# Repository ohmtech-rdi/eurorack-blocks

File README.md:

# eurorack-blocks

[<!--lint ignore no-dead-urls-->](https://github.com/ohmtech-rdi/eurorack-blocks/actions?workflow=Ubuntu%2020.04)
[<!--lint ignore no-dead-urls-->](https://github.com/ohmtech-rdi/eurorack-blocks/actions?workflow=macOS%2011)
[<!--lint ignore no-dead-urls-->](https://github.com/ohmtech-rdi/eurorack-blocks/actions?workflow=Windows%202019)

The `eurorack-blocks` project allows to develop your own custom Eurorack module for either
prototyping or fun in the comfort of your day-to-day IDE with the C++ or Faust language,
or using the Cycling '74 Max environment,
testing and debugging in a [virtual Eurorack environment](https://vcvrack.com),
and when ready, to auto-magically generate all the needed files to manufacture
the eurorack module for you to use in a real Eurorack modular system.

`eurorack-blocks` is using [`Daisy Patch Submodule`](https://www.electro-smith.com/daisy/patch-sm),
a DSP platform for Eurorack synthesizer modules. It features a lightning fast STM32 processor,
high fidelity stereo audio codec, and enough RAM for 10 minute long buffers
— all with standard signal levels and conditioning for the Eurorack ecosystem.

The [documentation as well as the Getting Started guide can be found on **Read the Docs**](https://eurorack-blocks.readthedocs.io/en/latest/).

The full project's manifest can be read [here](manifest.md).

```cpp
// Bypass.h

#include "artifacts/BypassUi.h"

struct Bypass {
   BypassUi ui;

   void process () {
      ui.audio_out = ui.audio_in;
   }
};
```

```erb
// Bypass.erbui

module Bypass {
   width 8hp
   material aluminum black
   header { label "BYPASS" }

   control audio_in AudioIn {
      position 4hp, 40mm
      label "IN"
   }

   control audio_out AudioOut {
      position 4hp, 80mm
      label "OUT"
   }
}
```

```console
raf:bypass$ erbb configure 👈 Generate IDE projects
raf:bypass$ ls -l artifacts/
drwxr-xr-x  7 raf  staff  224 Feb  9 18:31 actions
drwxr-xr-x  3 raf  staff   96 Feb  9 18:31 daisy 👈 Daisy firmware build files
drwxr-xr-x  3 raf  staff   96 Feb  9 18:31 simulator 👈 Simulator build files
-rw-r--r--  1 raf  staff  109 Feb  9 18:31 Bypass.code-workspace 👈 Visual Studio Code Workspace
drwxr-xr-x  3 raf  staff   96 Feb  9 18:31 project_vcvrack.xcodeproj 👈 Simulator Xcode Project
raf:bypass$ erbb build simulator 👈 Build the simulator for VCV Rack
...
** BUILD SUCCEEDED **
raf:bypass$ open /Applications/Rack.app 👈 Test in VCV Rack and iterate
raf:bypass$ erbb build hardware 👈 Build the hardware files for manufacturing
raf:bypass$ ls -l artifacts/hardware/
-rw-r--r--   1 raf  staff     387 Feb  9 18:31 Bypass.bom.csv 👈 Bill of materials
-rw-r--r--   1 raf  staff   15696 Feb  9 18:31 Bypass.dxf 👈 Aluminum panel milling/drilling
-rw-r--r--   1 raf  staff   32731 Feb  9 18:31 Bypass.gerber.zip 👈 PCB Gerber files
-rw-r--r--   1 raf  staff  116908 Feb  9 18:31 Bypass.kicad_pcb
-rw-r--r--   1 raf  staff    4754 Feb  9 18:31 Bypass.pdf 👈 Aluminum panel UV printing
drwxr-xr-x  12 raf  staff     384 Feb  9 18:31 gerber
raf:bypass$ erbb build 👈 Build the firmware
ninja: Entering directory `.../eurorack-blocks/samples/bypass/artifacts/daisy/out/Release'
[191/191] LINK Bypass
OBJCOPY Bypass
raf:bypass$ erbb install 👈 Upload the firmware
Enter the system bootloader by holding the BOOT button down,
and then pressing, and releasing the RESET button.
Press Enter to continue...
...
raf:bypass$
```

## Sample Projects

<p align="center">

</p>

Before reading sample code, make sure to grasp the concepts in the [documentation](https://eurorack-blocks.readthedocs.io/en/latest/).
Sample projects are a good place to continue learning:

- [`bypass`](./samples/bypass/) is the example used above,
- [`drop`](./samples/drop/) shows the usage of almost every blocks,
- [`reverb`](./samples/reverb/) illustrates how to utilize all the platform memory,
- [`kick`](./samples/kick/) illustrates how to use factory samples and make big programs,
- [`faust`](./samples/faust/) describes how to use the Faust functional programming language,
- [`custom`](./samples/custom/) illustrates how to use custom silkscreens, boards and manufacturers,
- [`frohmager`](./samples/frohmager/) is the recreation in hardware form factor of the legendary Ohm Force multi-band resonant filter (closed-source).

## Cycling '74 Max Patches

First make sure to read the [Max integration documentation](https://eurorack-blocks.readthedocs.io/en/latest/max/setup.html).
Sample projects are a good place to continue learning:

- [`reverb`](./max/reverb/) uses Gigaverb.
- [`drop`](./max/drop/) shows the usage of almost every blocks.

## Setting up

Setting up the development environment is described in the
[documentation](https://eurorack-blocks.readthedocs.io/en/latest/setup/select.html).
Integrations might have also their own Set up documentation, so make sure to read this as well.

## Structure

```
eurorack-blocks/
   blocks/
   boards/
   build-system/
   include/
   max/
   src/
   submodules/
```

- [`blocks`](./blocks/) contains all the atomic blocks hardware for design validation and software tests,
- [`boards`](./blocks/) contains all the boards hardware to design with,
- [`build-system`](./build-system/) contains the build system used to build and deploy
   the tests and samples,
- [`include`](./include/) contains the software implementation of the blocks,
- [`max`](./max/) contains the Cycling '74 Max integration,
- [`src`](./src/) contains the software implementation of the blocks,
- [`submodules`](./submodules/) contains the software dependencies as submodules.

## License

All files in this repository, excluding `submodules/`, are provided with the CC BY-SA 4.0 license
for the hardware part, and MIT license for the software part, **except**:

- The [Cycling '74 Max Gen DSP Source Code](./include/gen_dsp),
- The [D-DIN Font](./include/erb/vcvrack/design/d-din),
   under [SIL Open Font License](./include/erb/vcvrack/design/d-din/SIL%20Open%20Font%20License.txt),
- The [Indie Flower Font](./include/erb/vcvrack/design/indie-flower),
   under [SIL Open Font License](./include/erb/vcvrack/design/indie-flower/OFL.txt),
- The [Rogan... files](./include/erb/vcvrack/resource),
   as derivative work of some VCV Rack files under the [VCV Rack GPLv3 License](https://github.com/VCVRack/Rack/blob/v2/LICENSE-GPLv3.txt),
- The [Arpeggio project](https://github.com/textX/Arpeggio), under the [MIT License](https://textx.github.io/Arpeggio/stable/about/license/),
- The [Custom panel artwork](https://svgsilh.com/image/1532531.html), under the [Creative Commons CC0 License](https://creativecommons.org/publicdomain/zero/1.0/).
- The Ohm Force Frohmager, under its proprietary license.

Some files that get installed in `build-system/toolchain` during `erbb setup` are not part of this repository, but redistributed during the installation phase,
with the following licenses:
   - [dfu-util](https://dfu-util.sourceforge.net) under the [GPL version 2](https://sourceforge.net/p/dfu-util/dfu-util/ci/master/tree/COPYING),
   - [Cairo](https://www.cairographics.org) under the [GNU Lesser General Public License (LGPL) version 2.1 or the Mozilla Public License (MPL) version 1.1](https://gitlab.freedesktop.org/cairo/cairo/-/blob/master/COPYING),
   - [libcapstone](https://github.com/libcapstone/libcapstone) under the [3-Clause BSD License](https://github.com/libcapstone/libcapstone/blob/main/LICENSE.TXT),
   - [Fontconfig](https://www.freedesktop.org/wiki/Software/fontconfig/) under the [MIT License](https://gitlab.freedesktop.org/fontconfig/fontconfig/-/blob/main/COPYING),
   - [Freetype](https://freetype.org) under the [Freetype license or  GNU General Public License (GPL), version 2](https://freetype.org/license.html),
   - [libftdi](https://www.intra2net.com/en/developer/libftdi/), which [library is licensed under LGPL 2.1 (not any later)](http://developer.intra2net.com/git/?p=libftdi;a=blob;f=COPYING.LIB;h=5bc8fb2c8f757e34a0d8f4644f589d57609e213f;hb=HEAD), and [EEPROM programmer is licensed under GPL 2 (not any later)](http://developer.intra2net.com/git/?p=libftdi;a=blob;f=COPYING.GPL;h=d511905c1647a1e311e8b20d5930a37a9c2531cd;hb=HEAD),
   - [libhidapi](https://github.com/libusb/hidapi), under the [GNU General Public License, version 3.0](https://github.com/libusb/hidapi/blob/master/LICENSE-gpl3.txt), [BSD-Style License](https://github.com/libusb/hidapi/blob/master/LICENSE-bsd.txt) or [more liberal original HIDAPI license](https://github.com/libusb/hidapi/blob/master/LICENSE-orig.txt),
   - [libpixman](https://github.com/libpixman/pixman) under the [MIT license](https://github.com/libpixman/pixman/blob/master/COPYING),
   - [libpng](http://www.libpng.org/pub/png/libpng.html) under the [PNG Reference Library License version 2](http://www.libpng.org/pub/png/src/libpng-LICENSE.txt),
   - [libusb](https://github.com/libusb/libusb) under the [GNU Lesser General Public License v2.1](https://github.com/libusb/libusb/blob/master/COPYING),
   - [Xorg libraries](https://gitlab.freedesktop.org/xorg/lib) under the [MIT license](https://gitlab.freedesktop.org/xorg/lib/libx11/-/blob/master/COPYING),
   - [openocd](https://openocd.org) under the [GPL-2.0-or-later](https://sourceforge.net/p/openocd/code/ci/master/tree/COPYING)
   - [GNU Arm Embedded Toolchain](https://developer.arm.com/downloads/-/gnu-rm) under various licenses, navigate to `build-system/toolchain/gcc-arm-none-eabi-10.3-2021.10/share/doc/gcc-arm-none-eabi/license.txt` for a complete list,
   - [KiCad](https://www.kicad.org) under its [license](https://gitlab.com/kicad/code/kicad/-/blob/master/LICENSE).

Redistribution of your firmware for commecial purposes only have a subset of those licences:
- Modules which firmware was code generated by Gen from a patcher is dual licensed under the [Cycling '74 License for Max-Generated Code for Export](https://support.cycling74.com/hc/en-us/articles/10730031661587) or [GPLv3](https://www.gnu.org/licenses/gpl-3.0.en.html). 
- Eurorack-blocks framework is under the MIT license,
- [libDaisy](https://github.com/electro-smith/libDaisy) is under the [MIT license](https://github.com/electro-smith/libDaisy/blob/master/LICENSE),
- [GNU Arm Embedded Toolchain libraries](https://developer.arm.com/downloads/-/gnu-rm) under various licenses, navigate to `build-system/toolchain/gcc-arm-none-eabi-10.3-2021.10/share/doc/gcc-arm-none-eabi/license.txt` for a complete list.

Redistribution of your panel, if using the font in this repository:
- The [D-DIN Font](./include/erb/vcvrack/design/d-din), under [SIL Open Font License](./include/erb/vcvrack/design/d-din/SIL%20Open%20Font%20License.txt),

To fullfil attribution, users will generally put the ERB logo and the URL to this project, on their PCB like in [this example](https://blogger.googleusercontent.com/img/b/R29vZ2xl/AVvXsEjbp3qvEp6JkepX6Xh4_h2b57rY708SmwVZjv8ANe1bIvhrfsvV8bGgZkJezpeA5sWZmZln5WsoP8231fTwboIVxd3dbACfYKJyjOHhfvMlSTO7WLXSDi_nQDXI3Ygvw2XLOCR4dY4M1gGWNpXnzImI5TEGjqsB7BOLt36qAzrYm9yt0QguTqL6EOvM/s4032/TopographeBack.jpeg) (courtesy of [Oms in serial](https://omsinserial.blogspot.com))

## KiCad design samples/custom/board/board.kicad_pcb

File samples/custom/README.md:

# Custom

`Custom` is a sample to illustrate the use of custom images, boards and manufacturers.

[Artwork](https://svgsilh.com/image/1532531.html) from [Leunert](https://pixabay.com/users/leunert-2332372/) released under [Public Domain — Creative Commons CC0](https://creativecommons.org/publicdomain/zero/1.0/).

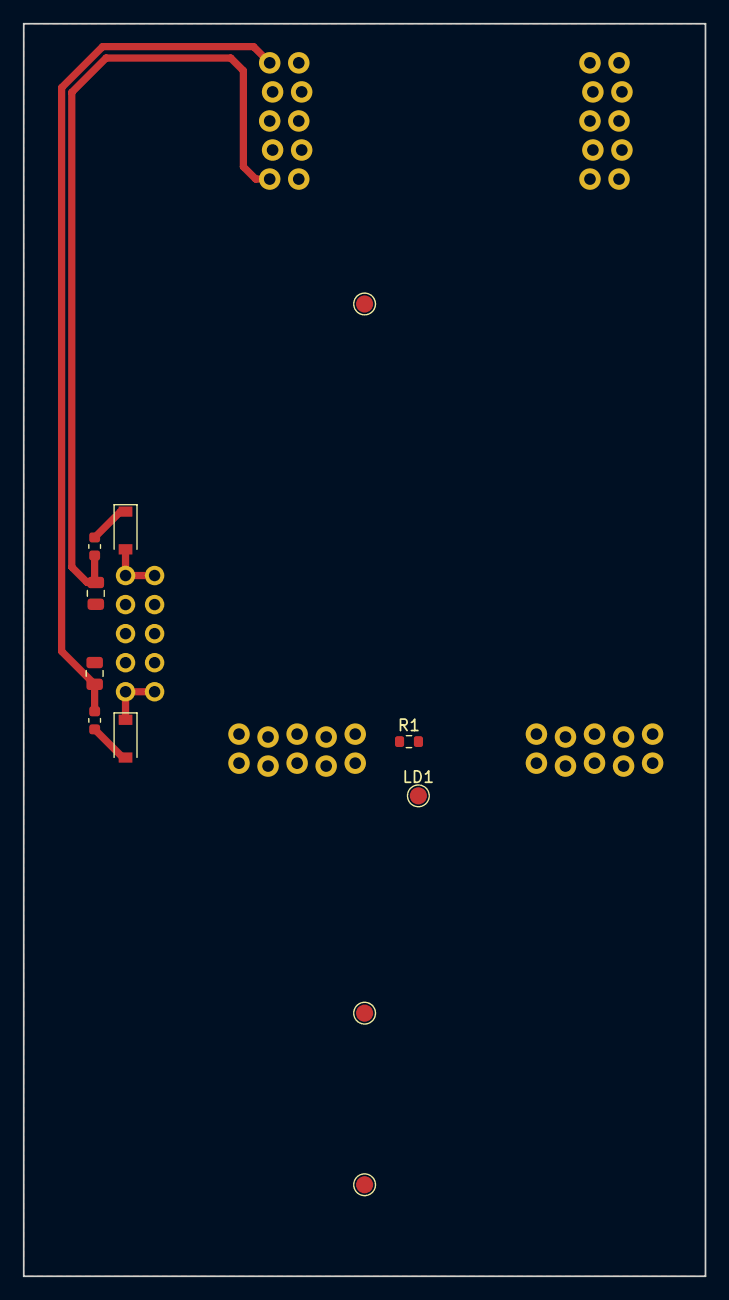
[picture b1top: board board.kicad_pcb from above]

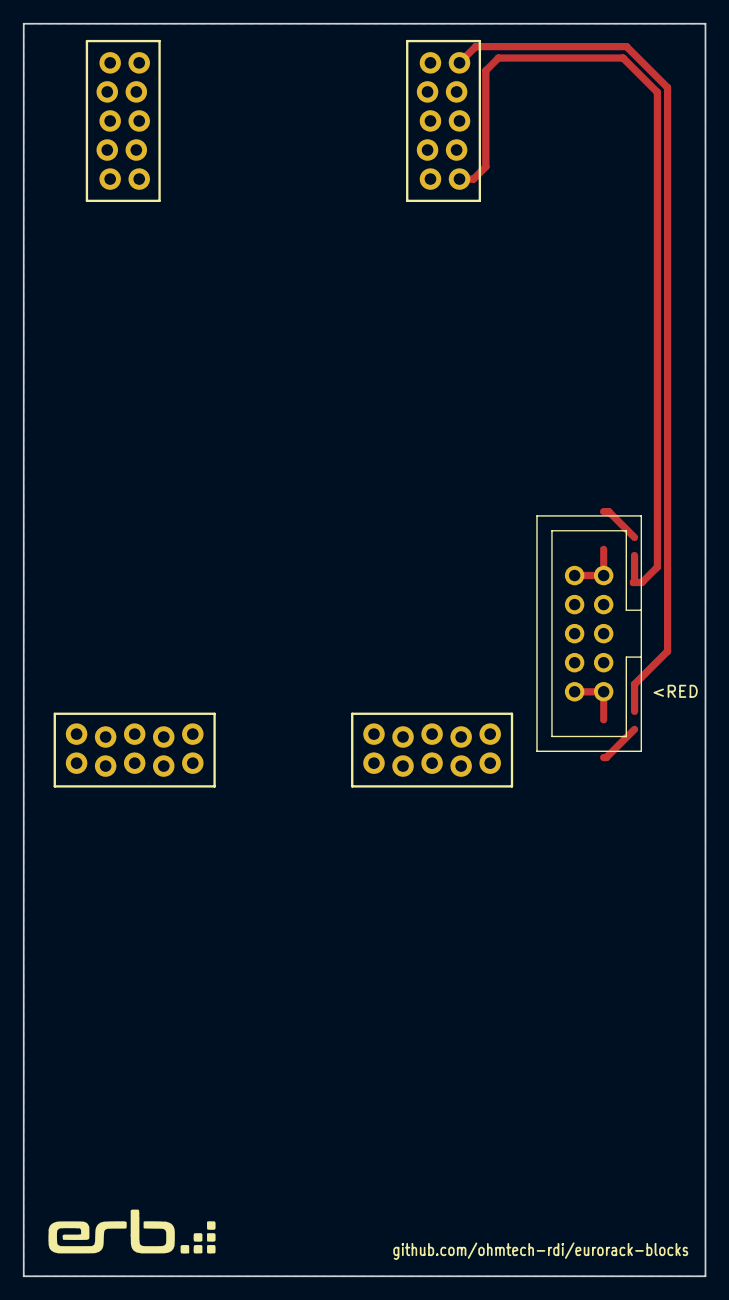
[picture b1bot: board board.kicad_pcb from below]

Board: 2 copper layers, 59.6 x 109.5 mm, 14 parts (2 on the bottom side), 12 nets.

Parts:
A1: DaisyPatchSm_Rev1; DaisyPatchSm
AI1: TestPoint; TestPoint_Pad_D1.5mm
AO1: TestPoint; TestPoint_Pad_D1.5mm
C1, C2: 10u; C_0805_2012Metric
D1, D2: D_Schottky; D_SOD-123
H1: ERB LOGO; ErbLog.15mm
J1: POWER BUS; IDC-Header_2x05_P2.54mm_Vertical
L1, L2: Ferrite_Bead; L_0603_1608Metric
LD1: TestPoint; TestPoint_Pad_D1.5mm
P1: TestPoint; TestPoint_Pad_D1.5mm
R1: 1k; R_0603_1608Metric

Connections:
+12V: A1.A5 (+12V), C1.1, L1.1
-12V: A1.A1 (-12V), C2.2, L2.1
/board.power/+12E: D1.2 (A), J1.9, J1.10
/board.power/-12E: D2.1 (K), J1.1, J1.2
AI1: A1.B4 (AUDIO_IN_L), AI1.1
AO1: A1.B2 (AUDIO_OUT_L), AO1.1
GND: A1.A4 (GND), A1.A7 (GND), A1.B3 (AUDIO_IN_R), C1.2, C2.1, J1.3, J1.4, J1.5, J1.6, J1.7, J1.8
LD1: LD1.1, R1.2
unnamed: A1.B5 (GATE_OUT_1), R1.1
unnamed: D1.1 (K), L1.2
unnamed: D2.2 (A), L2.2
P1: A1.D9 (SPI_MOSI), P1.1

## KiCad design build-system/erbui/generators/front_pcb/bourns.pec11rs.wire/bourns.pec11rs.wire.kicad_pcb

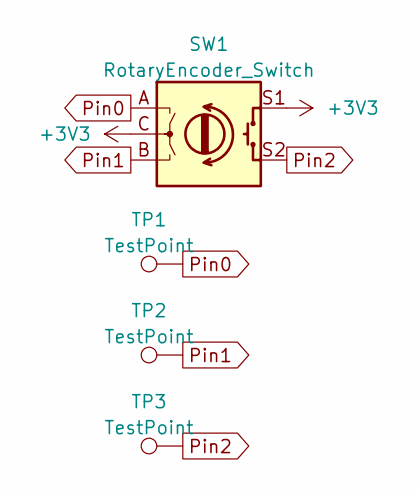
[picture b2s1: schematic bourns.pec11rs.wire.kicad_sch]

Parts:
SW1: RotaryEncoder_Switch; PEC11R-4220F-S0024
TP1, TP2, TP3: TestPoint; TestPoint_Pad_D1.5mm

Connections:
+3V3: SW1.C, SW1.S1
Pin0: SW1.A, TP1.1
Pin1: SW1.B, TP2.1
Pin2: SW1.S2, TP3.1

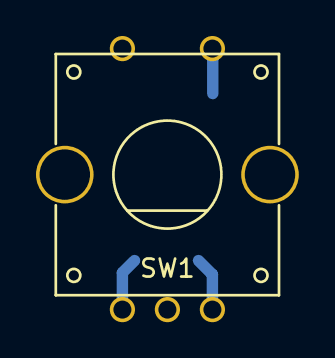
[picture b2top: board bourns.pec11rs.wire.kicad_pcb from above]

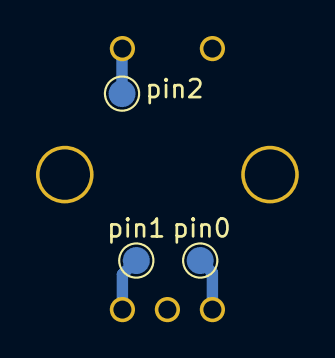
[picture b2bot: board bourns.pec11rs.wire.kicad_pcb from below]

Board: 2 copper layers, 4 parts (3 on the bottom side), 4 nets.

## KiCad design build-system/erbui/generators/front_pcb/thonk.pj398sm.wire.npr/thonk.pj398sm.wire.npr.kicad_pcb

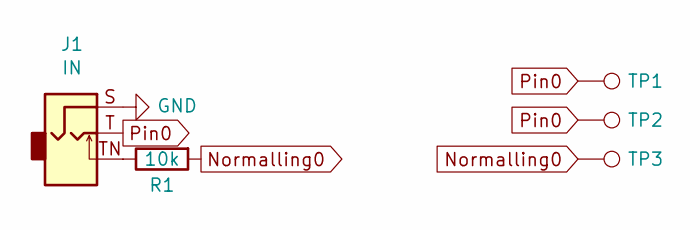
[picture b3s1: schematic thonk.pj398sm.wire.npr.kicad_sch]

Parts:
J1: IN; ThonkiconnJack
R1: 10k; R_Axial_DIN0207_L6.3mm_D2.5mm_P7.62mm_Horizontal
TP1, TP2, TP3: TestPoint; TestPoint_Pad_D1.5mm

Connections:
GND: J1.S
unnamed: J1.TN, R1.1
Normalling0: R1.2, TP3.1
Pin0: J1.T, TP1.1, TP2.1

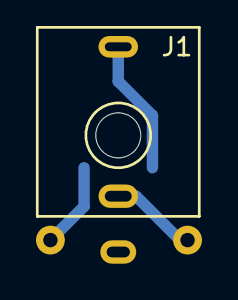
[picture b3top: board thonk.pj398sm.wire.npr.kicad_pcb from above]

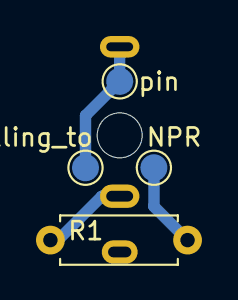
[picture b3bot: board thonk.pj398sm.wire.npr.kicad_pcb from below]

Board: 2 copper layers, 5 parts (4 on the bottom side), 3 nets.

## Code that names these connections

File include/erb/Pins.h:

/*****************************************************************************

      Pins.h
      Copyright (c) 2020 Raphael DINGE

*Tab=3***********************************************************************/



#pragma once



/*\\\ INCLUDE FILES \\\\\\\\\\\\\\\\\\\\\\\\\\\\\\\\\\\\\\\\\\\\\\\\\\\\\\\\*/

#include "daisy_core.h"



namespace erb
{



using Pin = dsy_gpio_pin;

static constexpr Pin Pin0 =  {DSY_GPIOB, 12};
static constexpr Pin Pin1 =  {DSY_GPIOC, 11};
static constexpr Pin Pin2 =  {DSY_GPIOC, 10};
static constexpr Pin Pin3 =  {DSY_GPIOC, 9};
static constexpr Pin Pin4 =  {DSY_GPIOC, 8};
static constexpr Pin Pin5 =  {DSY_GPIOD, 2};
static constexpr Pin Pin6 =  {DSY_GPIOC, 12};

static constexpr Pin Pin7 =  {DSY_GPIOG, 10};
static constexpr Pin Pin8 =  {DSY_GPIOG, 11};
static constexpr Pin Pin9 =  {DSY_GPIOB, 4};
static constexpr Pin Pin10 = {DSY_GPIOB, 5};
static constexpr Pin Pin11 = {DSY_GPIOB, 8};
static constexpr Pin Pin12 = {DSY_GPIOB, 9};
static constexpr Pin Pin13 = {DSY_GPIOB, 6};
static constexpr Pin Pin14 = {DSY_GPIOB, 7};

static constexpr Pin Pin15 = {DSY_GPIOC, 0};
static constexpr Pin Pin16 = {DSY_GPIOA, 3};
static constexpr Pin Pin17 = {DSY_GPIOB, 1};
static constexpr Pin Pin18 = {DSY_GPIOA, 7};
static constexpr Pin Pin19 = {DSY_GPIOA, 6};
static constexpr Pin Pin20 = {DSY_GPIOC, 1};
static constexpr Pin Pin21 = {DSY_GPIOC, 4};
static constexpr Pin Pin22 = {DSY_GPIOA, 5};

static constexpr Pin Pin23 = {DSY_GPIOA, 4};
static constexpr Pin Pin24 = {DSY_GPIOA, 1};
static constexpr Pin Pin25 = {DSY_GPIOA, 0};
static constexpr Pin Pin26 = {DSY_GPIOD, 11};
static constexpr Pin Pin27 = {DSY_GPIOG, 9};
static constexpr Pin Pin28 = {DSY_GPIOA, 2};
static constexpr Pin Pin29 = {DSY_GPIOB, 14};
static constexpr Pin Pin30 = {DSY_GPIOB, 15};

static constexpr Pin PinNC = {DSY_GPIOX, 0}; // internal

inline bool      operator == (const Pin & lhs, const Pin & rhs)
{
   return lhs.port == rhs.port && lhs.pin == rhs.pin;
}



struct AdcPin
{
   dsy_gpio_pin pin;
};

static constexpr AdcPin AdcPin0 =  {Pin15};
static constexpr AdcPin AdcPin1 =  {Pin16};
static constexpr AdcPin AdcPin2 =  {Pin17};
static constexpr AdcPin AdcPin3 =  {Pin18};
static constexpr AdcPin AdcPin4 =  {Pin19};
static constexpr AdcPin AdcPin5 =  {Pin20};
static constexpr AdcPin AdcPin6 =  {Pin21};
static constexpr AdcPin AdcPin7 =  {Pin22};
static constexpr AdcPin AdcPin8 =  {Pin23};
static constexpr AdcPin AdcPin9 =  {Pin24};
static constexpr AdcPin AdcPin10 = {Pin25};
static constexpr AdcPin AdcPin11 = {Pin28};



struct MultiplexerPin
{
   size_t pin;
};

static constexpr MultiplexerPin MultiplexerPin0 =  {0};
static constexpr MultiplexerPin MultiplexerPin1 =  {1};
static constexpr MultiplexerPin MultiplexerPin2 =  {2};
static constexpr MultiplexerPin MultiplexerPin3 =  {3};
static constexpr MultiplexerPin MultiplexerPin4 =  {4};
static constexpr MultiplexerPin MultiplexerPin5 =  {5};
static constexpr MultiplexerPin MultiplexerPin6 =  {6};
static constexpr MultiplexerPin MultiplexerPin7 =  {7};



struct MultiplexerAddressPins
{
   dsy_gpio_pin pin_a;
   dsy_gpio_pin pin_b;
   dsy_gpio_pin pin_c;
};



struct AudioInDaisyPin
{
   size_t pin;
};

static constexpr AudioInDaisyPin AudioInDaisyPinLeft =  {0};
static constexpr AudioInDaisyPin AudioInDaisyPinRight = {1};
static constexpr AudioInDaisyPin AudioInDaisyPin0 =     {0};
static constexpr AudioInDaisyPin AudioInDaisyPin1 =     {1};



struct AudioOutDaisyPin
{
   size_t pin;
};

static constexpr AudioOutDaisyPin AudioOutDaisyPinLeft =  {0};
static constexpr AudioOutDaisyPin AudioOutDaisyPinRight = {1};
static constexpr AudioOutDaisyPin AudioOutDaisyPin0 =     {0};
static constexpr AudioOutDaisyPin AudioOutDaisyPin1 =     {1};



}  // namespace erb



/*\\\ EOF \\\\\\\\\\\\\\\\\\\\\\\\\\\\\\\\\\\\\\\\\\\\\\\\\\\\\\\\\\\\\\\\\\*/

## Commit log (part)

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2023-09-18 fixup! Add seed2 dfm eval euro board
2023-09-18 Add tests for seed2 dfm eval euro board
2023-09-18 fixup! Add encoder
2023-09-18 Add display
2023-09-18 fixup! Add tests for seed2 dfm eval euro board
2023-09-18 fixup! Add display
2023-09-20 Revert use of aggregate initialization for libdaisy config
    libDaisy added user-declared constructors for default values which
    prevents using aggregate initialization.
2023-09-20 Update libdaisy submodule to v5.4.0 tag
2023-09-20 Refactor generators to allow multiple passes
2023-09-20 Add support for extra 3v3 power pins
2023-09-20 Add encoder support
2023-09-20 Add bourns pec11r no-switch part
2023-09-20 Add syntax highlighting support for encoder
2023-09-20 Add kicad bus support
2023-09-20 Fix net indexes in kicad pcb reloading
2023-09-20 Add support for rectangular shapes in kicad pcb parser
2023-09-20 Add support for rectangular cut-outs in dxf generator
2023-09-20 Add vcv rack support for custom/non-managed widgets
2023-09-20 Add display support
2023-09-20 Add east rising 128x64 spi display part
2023-09-20 Add FormatSsd130x data type support
2023-09-20 Add seed2 dfm eval euro board
2023-09-20 Add interactive test for seed2 dfm eval euro board
2023-09-20 Update documentation
2023-09-20 Fix pygments regex to match pins before pin
2023-09-20 Add syntax highlighting support for display
2023-12-06 Update gyp next submodule
    This fixes a problem where it was relying on distutils, which has been
    removed since python 3.12.
2023-12-06 Fix bootloader version in erbb install
2023-12-06 Fix missing E10 pin in seed2 dfm pin descriptions
2023-12-06 Update boards
2023-12-06 Add support for x and page offset in ssd130x implementation
2023-12-06 Update github workflows
2023-12-06 Update build scripts
2023-12-06 Update vcv rack sdk submodule
    The VCV Rack sdk version is now 2.4.0 which supports arm64 but also
    has a breaking change for plug-ins paths.
2023-12-06 Use vcv rack 2 native widgets for rogan and trim pot
    Native widgets have now more or less accurate physical dimensions, so
    use them.
2023-12-07 Remove unused files
2023-12-07 Derive missing rogan knobs
    Some files where just edited for colors, and the 1s knob was edited
    from the native rack 1ps.
2023-12-07 Use native vcv design for rogan knobs and trim pot
    Since rack 2, dimension are more accurate and design more beautiful,
    so let's use that instead.
2023-12-07 Update repository readme
    The license section needs to be updated, as we derive some work
    from vcv rack, which has a GPLv3 license.
2023-12-07 Add rogan 1s and 2s black knobs support to encoder
2023-12-07 Add rogan 1p knob support
2023-12-08 Add support for bootloader targets debugging
2023-12-08 Add src to workspace
2023-12-18 Fix graphic rect node generator
2023-12-19 Add rogan 3s knob support
2023-12-19 Add display rotation support
2023-12-19 Add invisible vcv widget
2023-12-20 Update generators
2023-12-20 Add encoder button class
2023-12-20 Update language
2023-12-20 Add switch version and refactor no-switch name
2023-12-20 Add simulator support
2023-12-20 Update tests
2023-12-27 Fix front panel rectangular hole
    We didn't check for rotation. This commit fixes that.
2023-12-31 Fix support for rectangular holes in pcb material
2023-12-31 Add support for kicad pcb gr_poly
2024-01-01 Fix widget to param id binding
2024-01-01 Update to bootloader v6
2024-01-01 Update bootloader path
2024-01-01 Update setup for bootloader v6
2024-01-01 Add bootloader fast boot option
2024-01-02 Fix image draw scaling and positioning problem
2024-01-02 Add layer concept to erbui language
2024-01-02 Add support for footprint zones and keepout zones in kicad pcb
2024-01-02 Add render mode concept to support translucency for panel generation
2024-01-02 Avoid calculating bounds for elements without one
    This typically happens for LEDs behind the panel. We can't really add
    a label since the element is not going through the panel, so it is
    expected the user won't use a label for those elements.
2024-01-02 Update xcode syntax highlighting
2024-01-02 Update vscode syntax highlighting
2024-01-02 Update part library
2024-01-02 Update samples
2024-01-02 Add discord badge on repository readme
2024-01-12 Fix solder mask
    Solder mask has an inverted logic, so it is needed to add it to the gerber
    so that it is effectively removed in production.
2024-01-12 Add proper support for multiple zone layers
2024-01-20 Generate warning on missing net
    This allows at least what to look for when editing the kicad_pcb file
    manually.
2024-01-20 Add support for gr_arc and ft_rect
2024-01-20 Add kicad pcb at class unlocked support
2024-01-22 Add vcv support for board format
2024-01-22 Add board format support
    This also adds implicitly height and 2.5d support with sides concept.
2024-01-22 Add vcv jack 6.35mm and footswitch widgets
2024-01-22 Add tayda drill generator
2024-01-22 Update syntax highlighters
2024-01-29 Rename GeneratorArg to Arg
    arg keyword will now be used outside of generator definitions
2024-01-29 Add args support to manufacturer control
2024-01-29 Add manufacturer control args support to style analyser
2024-01-29 Move switch number positions to manufacturer control definition
2024-01-29 Move display width & height to manufacturer control definition
2024-01-29 Move class keyword manufacturer control to arg
2024-01-29 Add leading type option to encoder
2024-01-31 Refactor qspi init in board implementation
    The comment was misleading: it's not that QSPI is already inited, it is
    that it is not possible to run from QSPI and have it memory mapped at the
    same time. To access QSPI, we need to have in the board, as while the
    private implementation is global, it is set in a QSPI instance only in
    Init.
2024-01-31 Move module init in onadd event
    We need to move module init after the module state is set, and this
    happens on onAdd event. This is preparation work for supporting
    dataFromJson initial state, which needs to run before the module is init.
2024-01-31 Add system HAL clock matching std chrono requirements
2024-01-31 Add load/save state to board concept
2024-01-31 Add persistent implementation
2024-01-31 Add interactive tests for display context
2024-01-31 Add display context
2024-01-31 Add github action ci checks for display context
2024-02-02 Handle persistent no rate limit case
    This is needed during a calibration phase, where we don't want rate
    limitation.
2024-02-02 Fix quantity for a reference counting by using number of references
    A same reference can be counted multiple time when split into different
    parts, eg. U1A, U1B, etc.
    Use the reference field to deduce quantity, because this is the ground
    truth.
2024-02-09 Add missing header
2024-02-17 Use equality operator to play nicer with standard library
2024-02-21 Fix module dragging in vcv when using invisible widgets
2024-02-21 Add invisible port simulator widget
2024-02-22 Add missing kicad footprint pad property solder mask margin and clearance
2024-02-27 Fix rotation for bottom parts
    In kicad, front part rotation is CCW but bottom part rotation is CW.
    Compensate for this when calculating rotation.
2024-02-28 Fix rotation for bottom parts
2024-03-02 Add precompiler flag to disable sdram usage
2024-03-02 Remove sdram related classes when sdram is not used
2024-03-04 Make perf template similar to firmware template
2024-03-07 Add fuzz testing system
2024-03-29 Add OLED SSD130x contrast control
2024-03-29 Separate concerns between value integrity and rate limiting
2024-05-25 Pin vcvrack version on windows
2024-05-25 Use O2 instead of O3
    This leads to smaller code size which has actually a beneficial impact
    on performance.
2024-05-27 Fix gyp file definition of buffer size and sample rate
    This is only used when generating the IDE projects. The defines are
    already done in the `erbb/vcvrack` generator, so they would conflict
    with the ones previously defined with a default value.
2024-05-29 Add sampling time and oversampling options to adc
2024-06-02 fixup! Update language
2024-06-02 Update gyp generator
2024-07-01 Add support for new rack folder introduced in vcv rack 2.5
2024-07-01 Update workflows
    macOS 11 image happens to be unavailable on the same day, so upgrade to
    macOS 12.
2024-07-08 Add 1590dd format support
2024-07-09 Add stereo audio support
2024-07-10 Add mxr knobs
2024-07-10 fixup! Add mxr knobs
2024-07-10 Add led 5mm bezel
2024-07-10 Add midi support
2024-07-10 fixup! Add midi support
2024-11-05 Use github math codeblock to render latex formulas
2024-11-24 Install faust from github releases
    Brew doesn't support macOS 12 anymore, so faust dependency libllvm needs
    to be compiled, which takes a lot of time. Install from binary
    distribution instead.
2024-11-24 Add support for er-oledm096-1 panel
2024-11-24 Add normalling pin abstraction
2024-11-24 fixup! Wip
2024-11-26 Fix parse error message
2024-11-26 Add erbb unit test target type feature
2024-12-06 Switch to macos13 in github workflows
2024-12-06 Add fatfs support
2024-12-06 Add 180 degree rotate for context output to display
2025-01-07 Add support for negative coordinates
2025-01-07 Add support for non standard hp size
2025-02-06 Add support for 36 hp size
2025-02-06 Add access to vcv module from erb board
2025-02-06 Add sdmmc support to language
2025-02-06 Add micro sd front pcb part
2025-02-06 Add sdmmc erb abstraction
2025-02-06 Add support for std::filesystem on macos
2025-02-06 Add sdmmc support to seed2 dfm euro eval board
2025-02-06 Add micro sd vcv widget
2025-02-06 Add sdmmc support to generators
2025-02-06 Remove test/seed2-dfm-eval-euro from windows workflow
    VCV needs -municode for build, which defines TCHAR as wchar_t while FatFs
    also defines this type to char. So we have a global namespace name clash
    we can't solve without changing FatFs implementation (which is available
    as a dependency inside libdaisy). We therefore remove the test and
    support for Windows.
2025-02-15 Debounce encoder
2025-03-12 Add front panel specs generator
2025-05-14 Read as binary, as the gzip check in cairo is expecting bytes, not str
2025-05-14 Remove ubuntu 20.04 workflows, as they are no longer supported on github
2025-05-20 Add support for string literal in erbb define declaration grammar
2025-05-21 Escape double quotes in makefile
    Double quotes have a meaning for Make, while we want to pass them
    verbatim. Escape them to achieve that.
2025-05-22 Add debouncing sliding window size configuration for encoder
2025-08-26 Switch to windows-2022 in github workflows
2025-08-26 Check the stack size only when building daisy
    The evaluation is not right on the desktop, as we are using 64-bit
    platforms, so that a lot of types takes much more than there 32-bit
    equivalent. There is not really a good way to assess that on the desktop,
    so remove this static assertion on it.
2026-02-25 Update libdaisy to v8.0.0 and a little commit with sd fix
2026-02-25 Update build system
    Paths and macros have changed. Since now CMSIS-DSP is part of libdaisy,
    we don't need __FPU_PRESENT anymore.
2026-02-25 Migrate to new daisy pin/gpio abstraction
2026-02-25 Quick fix failed builds
2026-03-11 Update libdaisy to v8.1.0 and a little commit with adc fix
2026-03-19 Add new reference_count member introduced in cairosvg 2.9.0
2026-04-22 Fix bootloader version
    Since the update of libdaisy, the bootloader is now v6.4. We need to
    update the version for the erbb install bootloader command.
2026-04-22 Add back pcb sd card reader widget

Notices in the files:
README.md:
License: CC BY-SA 4.0
